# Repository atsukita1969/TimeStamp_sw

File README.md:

# 8ボタン　IoTタイムスタンプ
ボタンを押したら、WEB上のgoogle spreadsheetに  
押したボタン番号と時間とステータス(0/1)が記録されます。  
コストパフォーマンス優先で、ESP32-C3-WROOM02-N4を使用しました。  
## Main PCB  

## Switch PCB  

## Switch BOX  

## spreadsheetの状態  

spreadsheetの設定は下記を参照。  
https://raspberry-pi.nomad-life.net/1917477/memo/esp32%e3%81%a7google%e3%82%b9%e3%83%97%e3%83%ac%e3%83%83%e3%83%89%e3%82%b7%e3%83%bc%e3%83%88%e3%81%ab%e6%9b%b8%e3%81%8d%e8%be%bc%e3%82%93%e3%81%a7%e3%81%bf%e3%82%8b/%e3%80%90arduino_ide%e3%80%91googlesheet%e3%81%ab%e6%9b%b8%e3%81%8d%e8%be%bc%e3%82%93%e3%81%a7%e3%81%bf%e3%81%9f  

（参考：https://www.haruirosoleil.com/entry/2020/02/02/101937）  
  
## arduino IDE書き込み設定  
arduino IDEの書き込み時の設定は下記。（USB-UARTブリッジ等を使わず、ESP32で内蔵USB-JTAGを使う場合）

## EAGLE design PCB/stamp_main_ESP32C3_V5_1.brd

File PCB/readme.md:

# PCB file
  
eagle / Fusion360

  ## ver 5.10 W/O JTAG bridge version

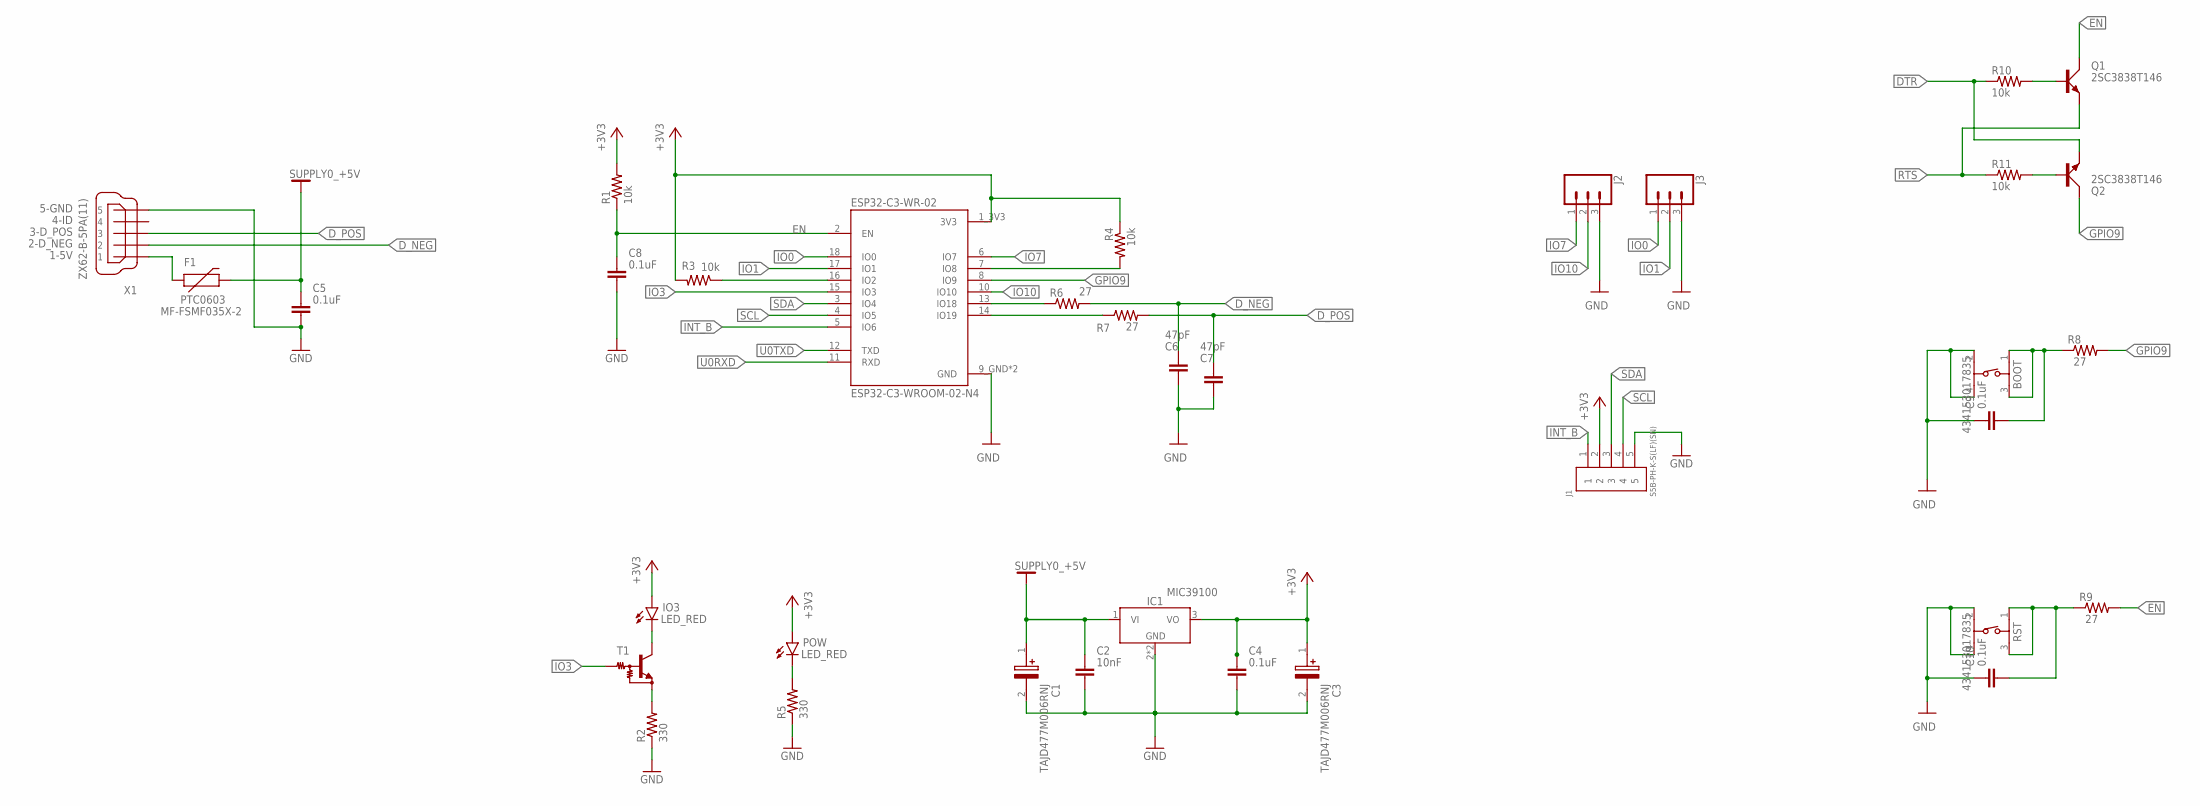
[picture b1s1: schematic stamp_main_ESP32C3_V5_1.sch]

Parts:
BOOT: 434153017835
C1, C3: TAJD477M006RNJ; CAPPM7344X310N
C2: 10nF; CAPC1608X85
C4, C5, C8, C9, C10: 0.1uF; CAPC1608X85
C6, C7: 47pF; CAPC2012X110
ESP32-C3-WR-02: ESP32-C3-WROOM-02-N4; MODULE_ESP32-C3-WROOM-02-H4
F1: PTC0603; 0603
IC1: LM7805_SOT223; SOT230P700X170-4
IO3: LED_RED; LEDC1608X39N_R
J1: S5B-PH-K-S(LF)(SN)
J2, J3: CONN_03; 1X03
POW: LED_RED; LEDC1608X39N_R
Q1, Q2: 2SC3838T146; SC59
R1, R3, R4, R10, R11: 10k; R0805
R2, R5: 330; R0805
R6, R7, R8, R9: 27; R0805
RST: 434153017835
T1: MUN2211T1-NPN_DRIVER-SC59-BEC; SC59-BEC
X1: ZX62-B-5PA(11)

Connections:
+3V3: C3.1 (+), C4.1, ESP32-C3-WR-02.1_3V3 (3V3), IC1.3 (VO), IO3.2 (A), J1.2, POW.2 (A), R1.2, R3.2, R4.1
+5V: C1.1 (+), C2.1, C5.1, F1.2, IC1.1 (VI)
DTR: Q2.E, R10.1
D_NEG: C6.1, R6.2, X1.2
D_POS: C7.1, R7.2, X1.3
EN: C8.1, ESP32-C3-WR-02.2 (EN), Q1.C, R1.1, R9.2
GND: BOOT.2 (3), BOOT.4, C1.2 (-), C2.2, C3.2 (-), C4.2, C5.2, C6.2, C7.2, C8.2, C9.1, C10.1, ESP32-C3-WR-02.9_GND (GND), ESP32-C3-WR-02.P$1_GND (GND), IC1.2 (GND), IC1.4 (GND), J1.5, J2.3, J3.3, R2.1, R5.1, RST.2 (3), RST.4, X1.5
GPIO9: ESP32-C3-WR-02.8 (IO9), Q2.C, R8.2
INT_B: ESP32-C3-WR-02.5 (IO6), J1.1
IO0: ESP32-C3-WR-02.18 (IO0), J3.1
IO1: ESP32-C3-WR-02.17 (IO1), J3.2
IO3: ESP32-C3-WR-02.15 (IO3), T1.B
IO7: ESP32-C3-WR-02.6 (IO7), J2.1
IO10: ESP32-C3-WR-02.10 (IO10), J2.2
unnamed: ESP32-C3-WR-02.16 (IO2), R3.1
unnamed: ESP32-C3-WR-02.7 (IO8), R4.2
unnamed: F1.1, X1.1
unnamed: C10.2, R9.1, RST.1, RST.3 (2)
unnamed: IO3.1 (C), T1.C
unnamed: BOOT.1, BOOT.3 (2), C9.2, R8.1
unnamed: Q1.B, R10.2
unnamed: Q2.B, R11.2
unnamed: POW.1 (C), R5.2
unnamed: R2.2, T1.E
unnamed: ESP32-C3-WR-02.13 (IO18), R6.1
unnamed: ESP32-C3-WR-02.14 (IO19), R7.1
RTS: Q1.E, R11.1
SCL: ESP32-C3-WR-02.4 (IO5), J1.4
SDA: ESP32-C3-WR-02.3 (IO4), J1.3
U0RXD: ESP32-C3-WR-02.11 (RXD)
U0TXD: ESP32-C3-WR-02.12 (TXD)

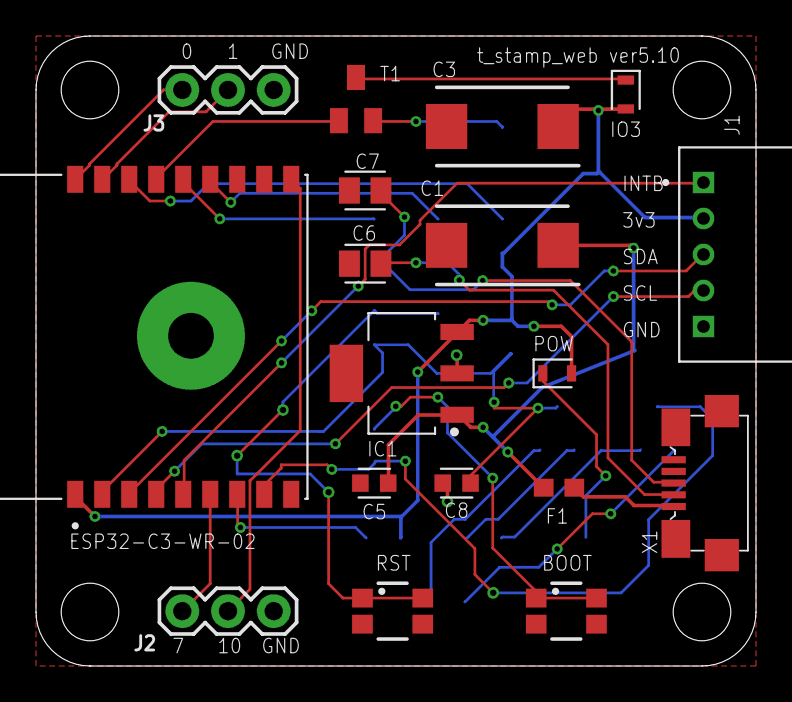
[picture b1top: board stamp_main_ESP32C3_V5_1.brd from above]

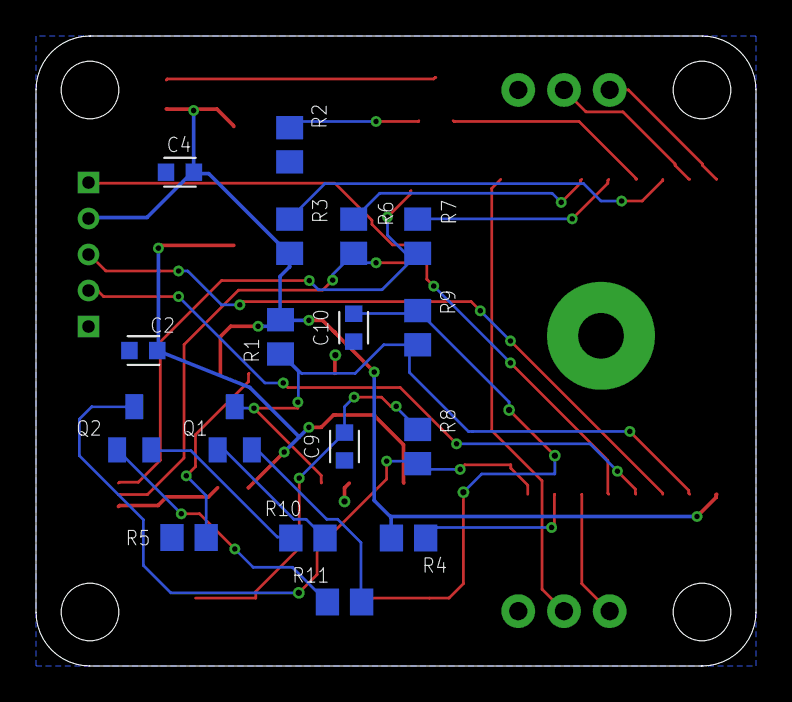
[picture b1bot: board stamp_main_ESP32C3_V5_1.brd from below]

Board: 2 copper layers, 40.0 x 35.0 mm, 35 parts (17 on the bottom side), 29 nets.

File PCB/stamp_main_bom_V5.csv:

Part,Value,Device,Package,Description
BOOT SW,EVQP2,EVQP2,EVQP2,SWITCH TACTILE SPST-NO 0.02A 15V
C1,6.3V/330uF,TAJC337K006RNJ,2312 / 6032,Tantalum Capacitors - Solid SMD 6.3volts 330uF 20%
C2,10nF,C_CHIP-0603(1608-METRIC),CAPC1608X85,Capacitor - Generic
C3,6.3V/330uF,TAJC337K006RNJ,2312 / 6032,Tantalum Capacitors - Solid SMD 6.3volts 330uF 20%
C4,0.1uF,C_CHIP-0603(1608-METRIC),CAPC1608X85,Capacitor - Generic
C5,0.1uF,C_CHIP-0603(1608-METRIC),CAPC1608X85,Capacitor - Generic
C6,47pF,C_CHIP-0805(2012-METRIC),CAPC2012X110,Capacitor - Generic
C7,47pF,C_CHIP-0805(2012-METRIC),CAPC2012X110,Capacitor - Generic
C8,0.1uF,C_CHIP-0603(1608-METRIC),CAPC1608X85,Capacitor - Generic
C9,0.1uF,C_CHIP-0603(1608-METRIC),CAPC1608X85,Capacitor - Generic
C10,0.1uF,C_CHIP-0603(1608-METRIC),CAPC1608X85,Capacitor - Generic
ESP32-C3-WR-02,ESP32-C3-WROOM-02-N4,ESP32-C3-WROOM-02-N4,MODULE_ESP32-C3-WROOM-02-H4,"WiFi Modules (802.11) (Engineering Samples) SMD module, ESP32-C3, 4MB SPI flash, PCB antenna, -40 C +105 C   Check availability  Check availability"
F1,PTC0603,PTC0603,0603,Resettable Fuse PTC
IC1,LM7805_SOT223,LM7805_SOT223,SOT230P700X170-4,5V Voltage Regulator
IO3 LED,LED_RED,LED_CHIP_RED-1608,LEDC1608X39N_R,LED - Generic
J1,S5B-PH-K-S(LF)(SN),S5B-PH-K-S(LF)(SN),S5B-PH-K-S(LF)(SN),JST PH conn (5)
J2,header pin (3),CONN_03,1X03,
J3,header pin (3),CONN_03,1X03,
POW LED,LED_RED,LED_CHIP_RED-1608,LEDC1608X39N_R,LED - Generic
Q1,2SC3838T146,2SC3838T146,SC59,NPN bi-pol transistor
Q2,2SC3838T146,2SC3838T146,SC59,NPN bi-pol transistor
R1,10k,R-US_R0805,R0805,"RESISTOR, American symbol"
R2,330ohm,R-US_R0805,R0805,"RESISTOR, American symbol"
R3,10k,R-US_R0805,R0805,"RESISTOR, American symbol"
R4,10k,R-US_R0805,R0805,"RESISTOR, American symbol"
R5,330ohm,R-US_R0805,R0805,"RESISTOR, American symbol"
R6,27ohm,R-US_R0805,R0805,"RESISTOR, American symbol"
R7,27ohm,R-US_R0805,R0805,"RESISTOR, American symbol"
R8,27ohm,R-US_R0805,R0805,"RESISTOR, American symbol"
R9,27ohm,R-US_R0805,R0805,"RESISTOR, American symbol"
R10,10k,R-US_R0805,R0805,"RESISTOR, American symbol"
R11,10k,R-US_R0805,R0805,"RESISTOR, American symbol"
RST SW,EVQP2,EVQP2,EVQP2,SWITCH TACTILE SPST-NO 0.02A 15V
T1,NPN digital transistor,NPN_DRIVER-SC59-BEC,SC59-BEC,NPN Bias Resistor Transistor
X1,ZX62-B-5PA(11),ZX62-B-5PA(11),ZX62-B-5PA(11),Micro USB Connector HI-SPEED Certified

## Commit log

2023-05-06 Create code

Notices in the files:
parts and their libraries:
SparkFun-Connectors: Licensing: Creative Commons ShareAlike 4.0 International - https://creativecommons.org/licenses/by-sa/4.0
Wurth_Switch_WS-TASV: Copyright: Würth Elektronik
